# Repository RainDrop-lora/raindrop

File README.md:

# RainDrop

Soil moisture monitoring system on LoRaWAN Network

## Problem

Resources watering city greenery are 
used sub-optimally.
It is complicated for the city to 
monitor work of subcontractors responsible
for city plants.
Rapidly changing climate makes watering an important task.

## Solution
System of wireless sensors that
measures soil moisture.

## Gains
* Municipality Gains means to evaluate work of subcontractors
* Community gains means to take care of community-planted trees
* Business gains means to optimally allocate resources 

## Architecture

## Results
* hardware prototype
* backend prototype
* cost analysis
* enduser application prototype
* all work is released under open source licence

## Plans
* order the first batch of PCBs next week
* work on battery life optimization
* deploy two LoRa gateways in next month

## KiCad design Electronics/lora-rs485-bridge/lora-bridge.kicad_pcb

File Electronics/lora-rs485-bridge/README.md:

# LoRa - RS485 bridge

This is a board that is specifically designed to easily hook up RS485 and I2C sensors to LoRaWAN network.

## Features

* Arduino compatible (Adafruit Feather M0 based)
* Low power:
  * Sleep current - 15uA
  * Message cost @ SF7 - 38mC (~190k messages from 4xAA battery)
  * Power switching for external I2C and RS485 sensors
* ESD protection
* Reverse polarity protection
* Wide input voltage range (up to 12V)
* Footprint for edge SMA antenna connector 

## Hardware resources

 * Connector J1 is power input, 12V max
 * Connector J4 is RS485 interface. VOUT on this connector is connected directly to the positive power input. Current of up to 500mA can be supplied from this connector. Q2 and Q1 form a high side switch to switch power to the connected RS485 bus. Digital pin **2** in Arduino environment can be used to switch power on and off.
 * Connector J3 is I2C interface. +3V3 on this connector is connected to the onboard +3V3 regulator. Up to 100mA can be supplied from this connector. R6 and R7 are I2C pullup resistors with the value of 4.7Ohm. Q7 is a switch that controls power to this connector. Digital pin **5** in Arduino environment can be used to controll this switch. Control logic is inverted, i.e. writing pin 5 HIGH will disconnect power to J3 and pullups, writing pin 5 LOW, will connect +3V3 to J3 and pullups.
 * SWD connector is provided for debugging and low level programming. 6-pin [Tag-Connect](https://www.tag-connect.com/product-category/products/cables/6-pin-target) connector can be used
 * Battery level is measured thru resistors R11, R12. Battery voltage is provided to this resistive divider when power to RS485 port is enabled. Voltage proportional to battery voltage is provided on analog pin **A0**. If using power supplies higher than 9V adjust values of resistors R11, R12 accordingly.
 * Led WAN is connected to digital pin **18**
 * Led SENS is connected to digital pin **17**
 * Led BATT is connected to digital pin **16**
 * Button TEST is connected to pin **A1**
 * Button RESET is connected to RESET line of the microcontroller U2.

## Power

The board is designed to be used with 4xAA 1.5V cells, actually physical dimensions of the board resemble a common cheap 4xAA holder. This strategy was chosen because for low power device it makes little sense to use recheargable batteries as you probably will not want to bring back device from field to charge it, it's much more practical to just change the batteries. 4xAA configuration allows to use up full capacity of AA cell - typically AA cells are totally flat at 0.8V, thus the circuit will stay fully operational till the batteries are flat - 0.8x4=3.2V while microcontroller works down to 2.5V and RFM69 module works down to 1.8V. 

Nevertheless, power sources up to 12V can be used. Also rechargeable LiPo cells can be used. 

## Antenna

A SMA connector is available on board, a right angle SMA connector designed for 1.6mm thickness board can be fitted. 

Nevertheless, a simple wire works just fine, I was able to transmit messages up to 10km away using a simple piece of wire as an antenna. Solder a piece of single core wire and cut it to a length for your frequency:
 * 868Mhz - 86.3mm
 * 915MHz - 81.9mm

## Firmware

A working example firmware source code is provided. The firmware takes care of setting up radio module, sleep, querying sensors and formatting payload and transmission. 

### Programming environment setup

A tutorial provided by [Adafruit for Feather M0 boards](https://learn.adafruit.com/adafruit-feather-m0-basic-proto/setup) can be followed for the programming environment setup. In a nutshell:

 * Use Arduino IDE version 1.8 or higher
 * Add this line to **Additional Boards Manager URLs** in preferences dialog: `https://adafruit.github.io/arduino-board-index/package_adafruit_index.json`
 * In the **Boards Manager** add support for **Arduino SAMD Boards** version 1.6.11 or later
 * In the **Boards Manager** add support for **Adafruit SAMD Boards**
 * In **Tools->Board** menu choose **Feather M0**; that's it, you are ready to go

### Libraries used

 * [arduino-lmic](https://github.com/mcci-catena/arduino-lmic) -- you can add it via Arduino Library manager, but cloning the git repo is strongly recommended to get all the latest fixes
 * [RTCZero](https://github.com/arduino-libraries/RTCZero) -- can be installed from Arduino Library manager

## Indication and UI

Three leds are provided on the board called WAN, SENS and BATT. It is up to the user to decide how exaclty to use them, but general guidance is that WAN led displays radio activity, SENS led provides sensor activity or status indication and BATT led provides battery status indication.

RESET and TEST buttons are available. RESET button resets the microcontroller, also it can be used to enter the bootloader mode for firmware upload. If sleep is utilised in the firmware, doubleclick the RESET button to enter the bootloader.

TEST button usage is up to the user.

Serial port is availale via USB-CDC interface, it can be used for debug messages, command line interface or other uses to be decided by the user. Note that in sleep mode USB is disconnected, disable sleep in the firmware to use the serial port.

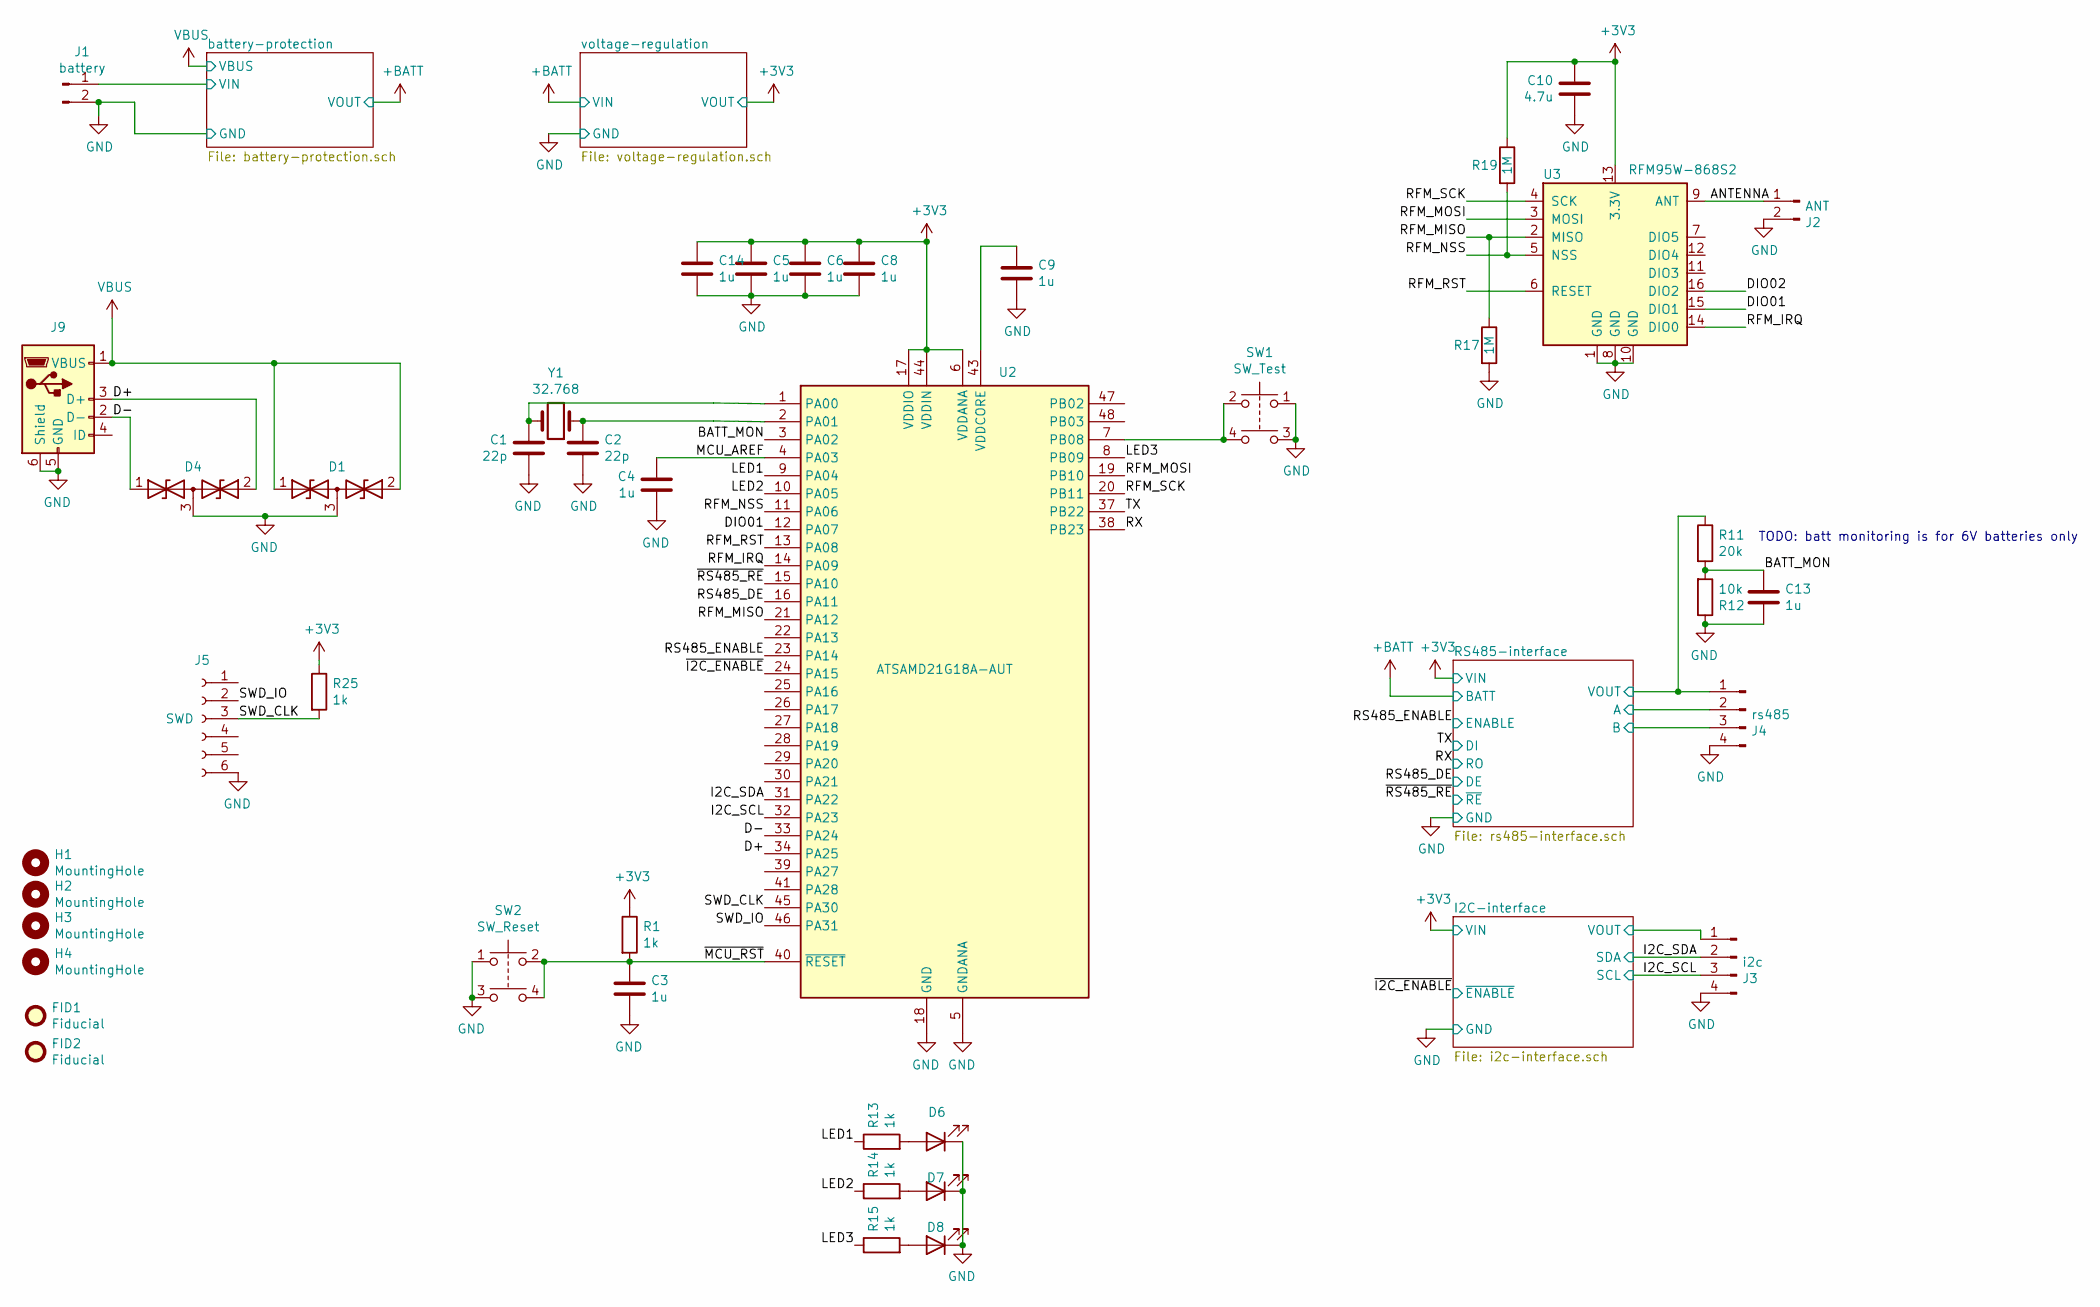
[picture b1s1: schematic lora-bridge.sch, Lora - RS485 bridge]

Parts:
C1, C2: 22p; C_0603_1608Metric
C3, C4, C5, C6, C8, C9, C13, C14: 1u; C_0603_1608Metric
C10: 4.7u; C_0603_1608Metric; PartNo C1608X5R1C475K080AE
D1, D4: D_TVS_x2_AAC; SC89; PartNo NZL5V6AXV3T1G
D6, D7, D8: LED; LED_0603_1608Metric
FID1, FID2: Fiducial; Fiducial_1mm_Dia_2mm_Outer
H1, H2, H3, H4: MountingHole; MountingHole_3.2mm_M3_DIN965
J1: battery; TerminalBlock_MetzConnect_Type101_RT01602HBWC_Pitch5.08mm
J2: ANT; SMA_6.35_EdgeMount; PartNo CON-SMA-EDGE-S
J3: i2c; TerminalBlock_MetzConnect_Type101_RT01604HBWC_Pitch5.08mm
J4: rs485; TerminalBlock_MetzConnect_Type101_RT01604HBWC_Pitch5.08mm
J5: SWD; TC2030-MCP-NL
J9: USB micro; USB_Micro-B_Vertical_Molex-105133-0001; PartNo 1051330011
R1, R13, R14, R15, R25: 1k; R_0603_1608Metric
R11: 20k; R_0603_1608Metric
R12: 10k; R_0603_1608Metric
R17, R19: 1M; R_0603_1608Metric
SW1: SW_Test; SW_Push_1P1T_NO_6x6mm_H9.5mm
SW2: SW_Reset; SW_Push_1P1T_NO_6x6mm_H9.5mm
U2: ATSAMD21G18A-AUT; TQFP-48_7x7mm_P0.5mm; PartNo ATSAMD21G18A-AUT
U3: RFM95W-868S2; RFM95; PartNo RFM95W-868S2
Y1: 32.768; Crystal_SMD_3215-2pin_3.2x1.5mm; PartNo FC-135 32.7680KA-A5

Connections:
+3V3: C5.1, C6.1, C8.1, C10.1, C14.1, R1.1, R19.1, R25.1, U2.6 (VDDANA), U2.17 (VDDIO), U2.36 (VDDIO), U2.44 (VDDIN), U3.13 (3.3V); also elsewhere on the board
/A: J4.2; also elsewhere on the board
/ANTENNA: J2.1, U3.9 (ANT)
/B: J4.3; also elsewhere on the board
/BATT_MON: C13.1, R11.2, R12.2, U2.3 (PA02)
/D+: D4.2 (A2), J9.3 (D+), U2.34 (PA25)
/D-: D4.1 (A1), J9.2 (D-), U2.33 (PA24)
/DIO01: U2.12 (PA07), U3.15 (DIO1)
/DIO02: U3.16 (DIO2)
/I2C_SCL: J3.3, U2.32 (PA23); also elsewhere on the board
/I2C_SDA: J3.2, U2.31 (PA22); also elsewhere on the board
/LED1: R13.1, U2.9 (PA04)
/LED2: R14.1, U2.10 (PA05)
/LED3: R15.1, U2.8 (PB09)
/MCU_AREF: C4.1, U2.4 (PA03)
/RFM_IRQ: U2.14 (PA09), U3.14 (DIO0)
/RFM_MISO: R17.1, U2.21 (PA12), U3.2 (MISO)
/RFM_MOSI: U2.19 (PB10), U3.3 (MOSI)
/RFM_NSS: R19.2, U2.11 (PA06), U3.5 (NSS)
/RFM_RST: U2.13 (PA08), U3.6 (RESET)
/RFM_SCK: U2.20 (PB11), U3.4 (SCK)
/RS485_DE: U2.16 (PA11); also elsewhere on the board
/RS485_ENABLE: U2.23 (PA14); also elsewhere on the board
/RX: U2.38 (PB23); also elsewhere on the board
/SWD_CLK: J5.3, R25.2, U2.45 (PA30)
/SWD_IO: J5.2, U2.46 (PA31)
/TX: U2.37 (PB22); also elsewhere on the board
/VIN: J1.1; also elsewhere on the board
/VOUT: J4.1, R11.1; also elsewhere on the board
/VOUT_1: J3.1; also elsewhere on the board
/~I2C_ENABLE: U2.24 (PA15); also elsewhere on the board
/~MCU_RST: C3.1, R1.2, SW2.2, SW2.4, U2.40 (~RESET)
/~RS485_RE: U2.15 (PA10); also elsewhere on the board
GND: C1.2, C2.2, C3.2, C4.2, C5.2, C6.2, C8.2, C9.2, C10.2, C13.2, C14.2, D1.3 (common), D4.3 (common), D6.1 (K), D7.1 (K), D8.1 (K), J1.2, J2.2, J3.4, J4.4, J5.6, J9.5 (GND), J9.6 (Shield), R12.1, R17.2, SW1.1, SW1.3, SW2.1, SW2.3, U2.5 (GNDANA), U2.18 (GND), U2.35 (GND), U2.42 (GND), U3.1 (GND), U3.8 (GND), U3.10 (GND); also elsewhere on the board
unnamed: C1.1, U2.1 (PA00), Y1.2
unnamed: C2.1, U2.2 (PA01), Y1.1
unnamed: C9.1, U2.43 (VDDCORE)
unnamed: D6.2 (A), R13.2
unnamed: D7.2 (A), R14.2
unnamed: D8.2 (A), R15.2
unnamed: SW1.2, SW1.4, U2.7 (PB08)
VBUS: D1.1 (A1), D1.2 (A2), J9.1 (VBUS); also elsewhere on the board

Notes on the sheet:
TODO: batt monitoring is for 6V batteries only

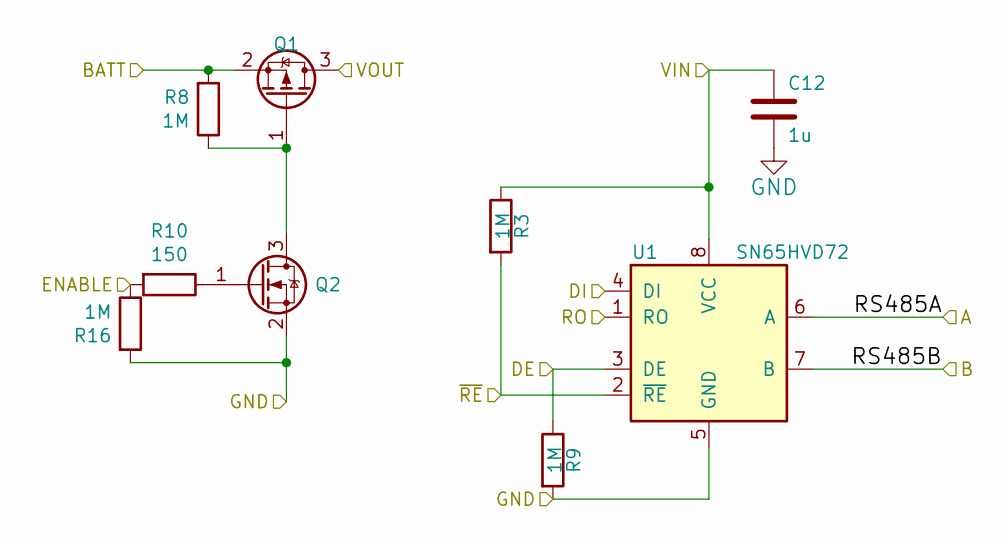
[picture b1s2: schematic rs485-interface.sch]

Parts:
C12: 1u; C_0603_1608Metric
Q1: Q_PMOS_GSD; SOT-23; PartNo NX2301P,215
Q2: Q_NMOS_GSD; SOT-23; PartNo NTR4003NT1G
R3, R8, R9, R16: 1M; R_0603_1608Metric
R10: 150; R_0603_1608Metric
U1: SN65HVD72; SOIC-8_3.9x4.9mm_P1.27mm; PartNo SN65HVD72DR

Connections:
+3V3: C12.1, R3.1, U1.8 (VCC); also elsewhere on the board
+BATT: Q1.2 (S), R8.2; also elsewhere on the board
/A: U1.6 (A); also elsewhere on the board
/B: U1.7 (B); also elsewhere on the board
/RS485_DE: R9.1, U1.3 (DE); also elsewhere on the board
/RS485_ENABLE: R10.2, R16.1; also elsewhere on the board
/RX: U1.1 (RO); also elsewhere on the board
/TX: U1.4 (DI); also elsewhere on the board
/VOUT: Q1.3 (D); also elsewhere on the board
/~RS485_RE: R3.2, U1.2 (~RE~); also elsewhere on the board
GND: C12.2, Q2.2 (S), R9.2, R16.2, U1.5 (GND); also elsewhere on the board
unnamed: Q1.1 (G), Q2.3 (D), R8.1
unnamed: Q2.1 (G), R10.1

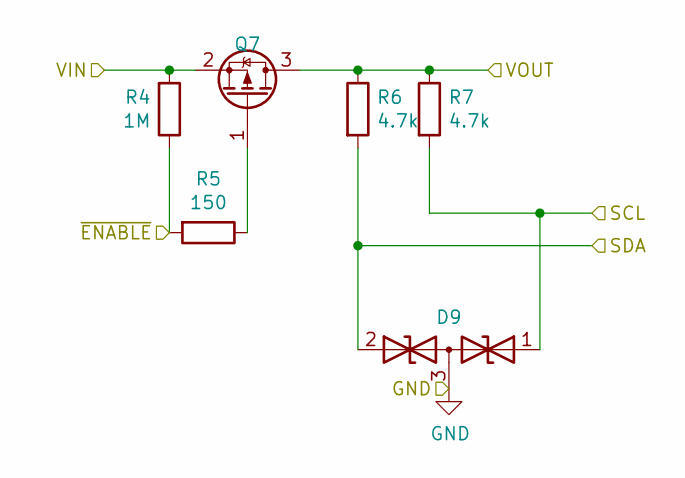
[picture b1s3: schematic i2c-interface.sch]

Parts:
D9: D_TVS_x2_AAC; SC89; PartNo NZL5V6AXV3T1G
Q7: Q_PMOS_GSD; SOT-23; PartNo NX2301P,215
R4: 1M; R_0603_1608Metric
R5: 150; R_0603_1608Metric
R6, R7: 4.7k; R_0603_1608Metric

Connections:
+3V3: Q7.2 (S), R4.2; also elsewhere on the board
/I2C_SCL: D9.1 (A1), R7.2; also elsewhere on the board
/I2C_SDA: D9.2 (A2), R6.2; also elsewhere on the board
/VOUT_1: Q7.3 (D), R6.1, R7.1; also elsewhere on the board
/~I2C_ENABLE: R4.1, R5.2; also elsewhere on the board
GND: D9.3 (common); also elsewhere on the board
unnamed: Q7.1 (G), R5.1

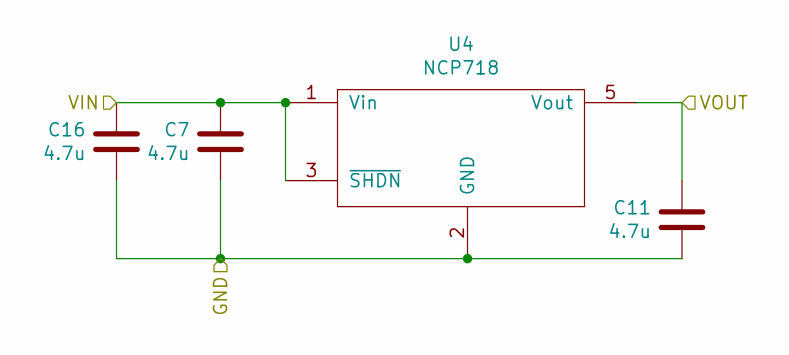
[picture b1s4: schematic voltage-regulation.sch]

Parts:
C7, C11, C16: 4.7u; C_0603_1608Metric; PartNo C1608X5R1C475K080AE
U4: NCP718; SOT-23-5; PartNo NCP718ASN330T1G

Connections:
+3V3: C11.1, U4.5 (Vout); also elsewhere on the board
+BATT: C7.1, C16.1, U4.1 (Vin), U4.3 (~SHDN); also elsewhere on the board
GND: C7.2, C11.2, C16.2, U4.2 (GND); also elsewhere on the board

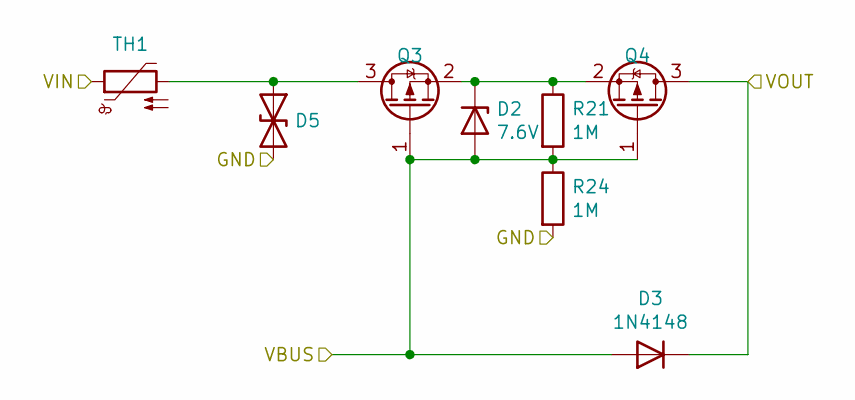
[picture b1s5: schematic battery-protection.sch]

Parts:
D2: 7.6V; D_SOD-323; PartNo MM3Z7V5ST1G
D3: 1N4148; D_SOD-123; PartNo 1N4148W-7-F
D5: D_TVS; D_SOD-123F; PartNo SMF11A
Q3, Q4: Q_PMOS_GSD; SOT-23; PartNo NX2301P,215
R21, R24: 1M; R_0603_1608Metric
TH1: Thermistor_PTC; Fuse_1206_3216Metric; PartNo nSMD075-13.2V

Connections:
+BATT: D3.1 (K), Q4.3 (D); also elsewhere on the board
/VIN: TH1.1; also elsewhere on the board
GND: D5.2 (A2), R24.2; also elsewhere on the board
unnamed: D2.1 (K), Q3.2 (S), Q4.2 (S), R21.1
unnamed: D5.1 (A1), Q3.3 (D), TH1.2
VBUS: D2.2 (A), D3.2 (A), Q3.1 (G), Q4.1 (G), R21.2, R24.1; also elsewhere on the board

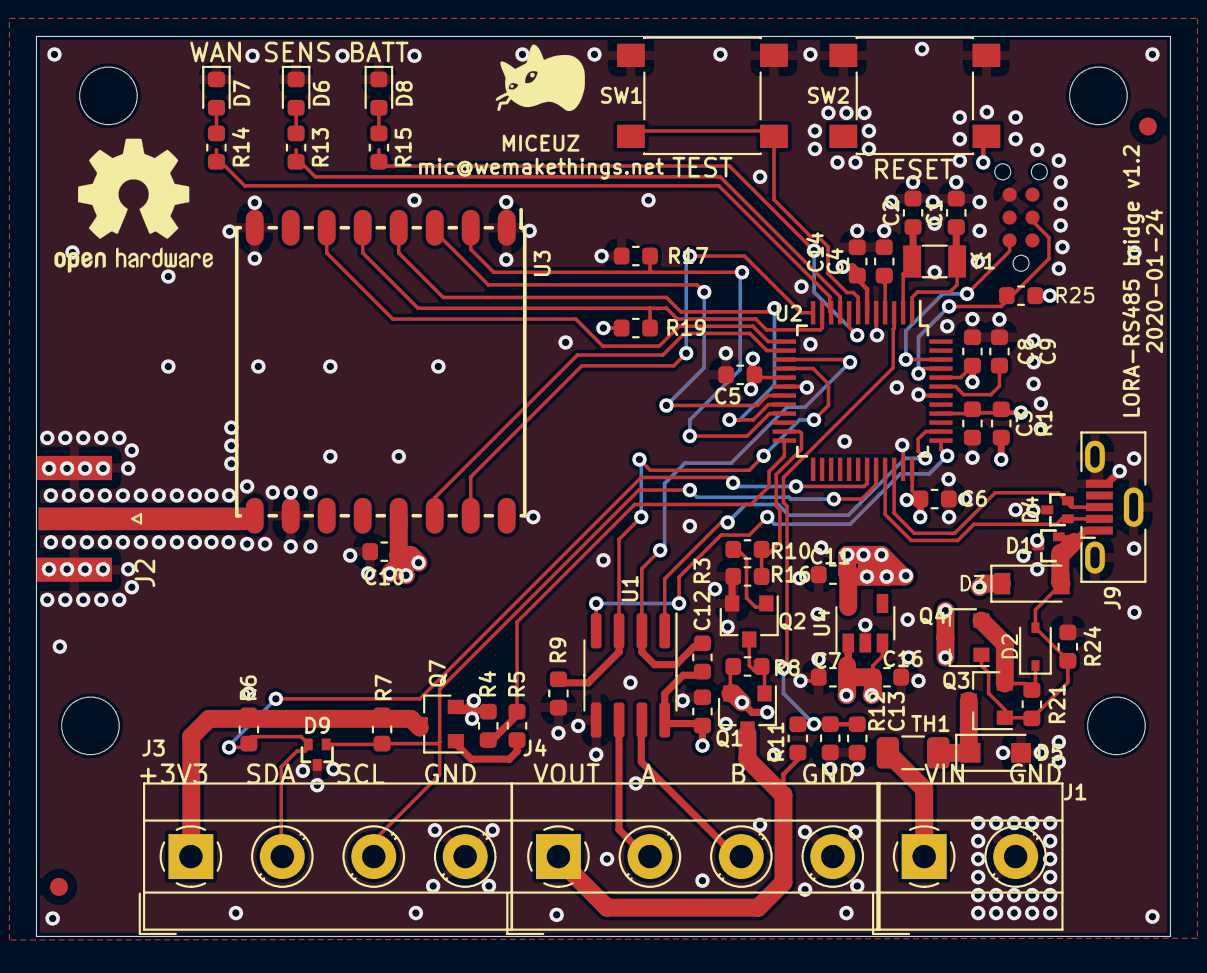
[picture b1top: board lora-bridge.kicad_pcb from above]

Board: 4 copper layers, 63.0 x 50.0 mm, 69 parts (0 on the bottom side), 47 nets.

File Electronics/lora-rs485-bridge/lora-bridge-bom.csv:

"Item","Qty","Reference(s)","Value","Footprint","DNP","PartNo","Manufacturer","Comment"
"1","2","C1, C2","22p","Capacitor_SMD:C_0603_1608Metric","","","",""
"2","9","C3, C4, C5, C6, C8, C9, C12, C13, C14","1u","Capacitor_SMD:C_0603_1608Metric","","","","Generic X5R capacitor"
"3","4","C7, C10, C11, C16","4.7u","Capacitor_SMD:C_0603_1608Metric","","C1608X5R1C475K080AE","TDK",""
"4","3","D1, D4, D9","D_TVS_x2_AAC","miceuz-lib:SC89",""," NZL5V6AXV3T1G","ON SEMICONDUCTOR",""
"5","1","D2","7.6V","Diode_SMD:D_SOD-323","","MM3Z7V5ST1G","ON SEMI",""
"6","1","D3","1N4148","Diode_SMD:D_SOD-123","","1N4148W-7-F","Diodes Inc",""
"7","1","D5","D_TVS","Diode_SMD:D_SOD-123F","","SMF11A","Littlefuse",""
"8","3","D6, D7, D8","LED","LED_SMD:LED_0603_1608Metric","","","",""
"9","1","J1","battery","TerminalBlock_MetzConnect:TerminalBlock_MetzConnect_Type101_RT01602HBWC_Pitch5.08mm","","","",""
"10","1","J2","ANT","miceuz-lib:SMA_6.35_EdgeMount","","CON-SMA-EDGE-S","RF Solutions","Can be replaced with compatible footprint connector specified up to 3GHz, VSWR < 1.2"
"11","1","J3","i2c","TerminalBlock_MetzConnect:TerminalBlock_MetzConnect_Type101_RT01604HBWC_Pitch5.08mm","","","",""
"12","1","J4","rs485","TerminalBlock_MetzConnect:TerminalBlock_MetzConnect_Type101_RT01604HBWC_Pitch5.08mm","","","",""
"13","1","J5","SWD","miceuz-lib:TC2030-MCP-NL","DNP","","",""
"14","1","J9","USB micro","Connectors_USB:USB_Micro-B_Vertical_Molex-105133-0001","","1051330011","MOLEX",""
"15","4","Q1, Q3, Q4, Q7","Q_PMOS_GSD","Package_TO_SOT_SMD:SOT-23","","NX2301P,215 ","NXP","Exact as specified"
"16","1","Q2","Q_NMOS_GSD","Package_TO_SOT_SMD:SOT-23","","NTR4003NT1G","ON SEMICONDUCTOR",""
"17","5","R1, R13, R14, R15, R25","1k","Resistor_SMD:R_0603_1608Metric","","","",""
"18","9","R3, R4, R8, R9, R16, R17, R19, R21, R24","1M","Resistor_SMD:R_0603_1608Metric","","","","Generic 5% resistor"
"19","2","R5, R10","150","Resistor_SMD:R_0603_1608Metric","","","",""
"20","2","R6, R7","4.7k","Resistor_SMD:R_0603_1608Metric","","","",""
"21","1","R11","20k","Resistor_SMD:R_0603_1608Metric","","","",""
"22","1","R12","10k","Resistor_SMD:R_0603_1608Metric","","","",""
"23","1","SW1","SW_Test","Button_Switch_SMD:SW_Push_1P1T_NO_6x6mm_H9.5mm","","","",""
"24","1","SW2","SW_Reset","Button_Switch_SMD:SW_Push_1P1T_NO_6x6mm_H9.5mm","","","",""
"25","1","TH1","Thermistor_PTC","Fuse:Fuse_1206_3216Metric","","nSMD075-13.2V","TECHFUSE",""
"26","1","U1","SN65HVD72","Package_SO:SOIC-8_3.9x4.9mm_P1.27mm","","SN65HVD72DR","TEXAS INSTRUMENTS",""
"27","1","U2","ATSAMD21G18A-AUT","Package_QFP:TQFP-48_7x7mm_P0.5mm","","ATSAMD21G18A-AUT","Microchip",""
"28","1","U3","RFM95W-868S2","miceuz-lib:RFM95","","RFM95W-868S2","HopeRF",""
"29","1","U4","NCP718","TO_SOT_Packages_SMD:SOT-23-5","","NCP718ASN330T1G","ON SEMICONDUCTOR",""
"30","1","Y1","32.768","Crystals:Crystal_SMD_3215-2pin_3.2x1.5mm","","FC-135 32.7680KA-A5","EPSON",""

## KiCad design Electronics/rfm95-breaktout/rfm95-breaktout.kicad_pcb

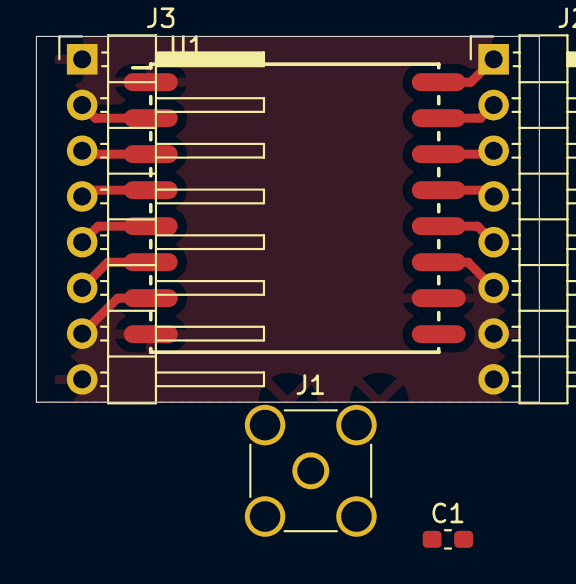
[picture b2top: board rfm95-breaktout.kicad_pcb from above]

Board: 2 copper layers, 27.9 x 20.3 mm, 5 parts (0 on the bottom side), 14 nets.

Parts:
C1: C; C_0603_1608Metric_Pad1.05x0.95mm_HandSolder
J1: ANT; SMA_Amphenol_901-144_Vertical
J2, J3: Conn_01x08; Pin_Header_Angled_1x08_Pitch2.54mm
U1: RFM95W-868S2; RFM95

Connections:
+3V3: C1.1, J2.4, U1.13
/ANT: J1.1, U1.9
/DIO01: J2.2, U1.15
/DIO02: J2.1, U1.16
/DIO03: J2.6, U1.11
/DIO04: J2.5, U1.12
/DIO5: J3.7, U1.7
/RFM_IRQ: J2.3, U1.14
/RFM_MISO: J3.2, U1.2
/RFM_MOSI: J3.3, U1.3
/RFM_NSS: J3.5, U1.5
/RFM_RST: J3.6, U1.6
/RFM_SCK: J3.4, U1.4
GND: C1.2, J1.2, J2.7, J3.1, J3.8, U1.1, U1.8, U1.10

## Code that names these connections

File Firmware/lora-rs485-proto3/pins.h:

#define DE          0
#define RE          1
#define LED_WAN     18
#define LED_SENSOR  17
#define LED_BATT    16
#define RS_485_EN   2
#define I2C_EN      5

#define RFM_NSS     8
#define RFM_RST     4
#define RFM_IRQ     3
#define RFM_DIO01   9

#define i2cEnable() digitalWrite(I2C_EN, LOW)
#define i2cDisable() digitalWrite(I2C_EN, HIGH)
#define rs485Enable() digitalWrite(RS_485_EN, HIGH)
#define rs485Disable() digitalWrite(RS_485_EN, LOW)
#define rs485Sleep() digitalWrite(RE, HIGH); digitalWrite(DE, LOW)
#define rs485DriverEnable()   digitalWrite(RE, HIGH); digitalWrite(DE, HIGH)
#define rs485ReaderEnable()   digitalWrite(DE, LOW); digitalWrite(RE, LOW)

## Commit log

2019-09-21 Add basic test firmware. Works.
2019-09-21 Add electronics designed so far
2019-09-21 Add price calculation for hardware
2019-09-21 Make more calculations
2019-09-21 Ignore temporary libreoffice files
2019-09-21 Some PCB routing is done
2019-09-22 Add readme and presentation
2019-09-22 Infra scripts added
2019-09-22 Empty dirs added
2019-11-04 Add ESD protection to i2c lines, change VIN TVS diode to higher voltage, add series resistors to SPI lines, compress the PCB to be at width of typical 4xAA battery holder
2020-01-10 Add firmware experiments
2020-01-10 Add power input PTC fuse
2020-01-10 Add some 3d models and colateral documentation
2020-01-10 Add manufacturing files
2020-01-10 Add related documentation
2020-01-10 Add 3rd version of firmware. rs485 functionality up and running
2020-01-10 Improve modbus comm debug message, add possible sleep hang fix to proto2 firmware
2020-01-14 Add pullup to SWDCLK for better stability. Change reset pullup value to 1k
2020-01-17 Add some initial documentation
2020-01-17 Fix info on silkscreen, remove RF connector pads from paste layer
2020-01-24 Move R11 and accompanying components a bit so it's easier to replace it. Add fiducials. Generate gerbers for v1.2
2020-02-21 Move around vias so power planes are not so much broken. Move connectors closer together so all of them are on 5.08mm grid
2020-02-21 Just a touch
2020-03-17 Refactor code, split it up to functional blocks
2020-03-23 Tune up prototype1 FW for board testing, chase kicad format changes
2020-03-23 Add more documentation
